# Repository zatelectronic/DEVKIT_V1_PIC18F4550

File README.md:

<div align="center">

# DEVKIT V1 PIC18F4550

**Kit de desenvolvimento profissional para o microcontrolador PIC18F4550 com USB nativo, programação via conector ICSP compatível com programador externo, reguladores 5V e 3,3V, oscilador SMD, botões RESET e BOOT, 2 LEDs de status e exposição completa de todos os ports GPIO**

</div>

---

## 📋 Índice

- [DEVKIT V1 PIC18F4550](#devkit-v1-pic18f4550)
  - [📋 Índice](#-índice)
  - [Visão Geral](#visão-geral)
  - [Renders 3D](#renders-3d)
  - [Arquitetura do Projeto](#arquitetura-do-projeto)
  - [Funcionalidades](#funcionalidades)
  - [Especificações Técnicas](#especificações-técnicas)
  - [Arquitetura de Alimentação](#arquitetura-de-alimentação)
  - [Interface USB Nativa](#interface-usb-nativa)
  - [Conector ICSP — Programação](#conector-icsp--programação)
    - [J5 — ICSP Principal (6 pinos angulado)](#j5--icsp-principal-6-pinos-angulado)
    - [J6 — Conector Auxiliar (3 pinos)](#j6--conector-auxiliar-3-pinos)
  - [Mapa Completo de Conectores e GPIO](#mapa-completo-de-conectores-e-gpio)
    - [J1 — Alimentação Externa (2 pinos)](#j1--alimentação-externa-2-pinos)
    - [J2 — Port RA (5 pinos)](#j2--port-ra-5-pinos)
    - [J3 — Port RC Superior (3 pinos)](#j3--port-rc-superior-3-pinos)
    - [J4 — Port RC Inferior (6 pinos)](#j4--port-rc-inferior-6-pinos)
    - [J7 — Port RE (4 pinos)](#j7--port-re-4-pinos)
    - [J8 — Port RB (4 pinos)](#j8--port-rb-4-pinos)
    - [J9 — Port RD (8 pinos)](#j9--port-rd-8-pinos)
    - [J10 — Alimentações (3 pinos)](#j10--alimentações-3-pinos)
  - [Lista de Materiais](#lista-de-materiais)
    - [Microcontrolador](#microcontrolador)
    - [USB Type-C e Alimentação](#usb-type-c-e-alimentação)
    - [Programador ICSP](#programador-icsp)
    - [Conectores GPIO](#conectores-gpio)
  - [Estrutura do Repositório](#estrutura-do-repositório)
  - [Como Usar](#como-usar)
    - [1. Gravando firmware via ICSP](#1-gravando-firmware-via-icsp)
    - [2. Alimentação](#2-alimentação)
    - [3. Modo Bootloader USB (BOOT)](#3-modo-bootloader-usb-boot)
    - [Exemplo de código — MPLAB XC8](#exemplo-de-código--mplab-xc8)
    - [Ferramentas recomendadas](#ferramentas-recomendadas)
  - [Sobre](#sobre)

---

## Visão Geral

**DEVKIT V1 PIC18F4550** é um kit de desenvolvimento completo para o microcontrolador **PIC18F4550-IPT** (TQFP-44 SMD), projetado pela **ZAT ELECTRONIC** utilizando **KiCad 10** com esquemático hierárquico dividido em quatro sub-folhas: **Microcontrolador**, **USB Type-C**, **Programador ICSP** e **Conexões GPIO**.

O PIC18F4550 é um microcontrolador de 8 bits da família PIC18 com **USB 2.0 Full Speed nativo** (RC4/D− e RC5/D+), memória Flash de 32KB, SRAM de 2KB e EEPROM de 256 bytes. O DEVKIT expõe todos os ports GPIO (RA, RB, RC, RD, RE) em conectores fêmea de 2,54mm, inclui reguladores de tensão **5V** e **3,3V** on-board, oscilador a cristal SMD de **8MHz**, botões **RESET** e **BOOT** tácteis SMD, **2 LEDs SMD** de status e conector **ICSP de 6 pinos** angulado compatível com programador externo.

> 💡 O modelo 3D do programador externo (`Microchip - PICkit3.stp`) está incluído no projeto — as imagens 3D mostram o DEVKIT conectado a um programador externo, evidenciando a integração direta pelo conector ICSP lateral.

---

## Renders 3D

<div align="center">

*Vista superior — PIC18F4550 TQFP-44, USB-C, cristal SMD, botões RESET/BOOT e conectores GPIO*

<br/>

*Vista isométrica — DEVKIT conectado ao programador externo pelo conector ICSP de 6 pinos*

<br/>

*Vista inferior isométrica — exposição completa dos ports RD (8 pinos) e RB (4 pinos) na borda inferior*

<br/>

*Visão completa do ecossistema — DEVKIT + programador externo para gravação de firmware*

</div>

---

## Arquitetura do Projeto

O projeto é organizado em **esquemático hierárquico** com 4 sub-folhas independentes:

```
DEVKIT_V1_PIC18F4550.kicad_sch  (folha raiz)
│
├── MICROCONTROLADOR.kicad_sch
│   ├── PIC18F4550-IPT (TQFP-44)
│   ├── Cristal 8MHz HC-49/SD SMD (KR1)
│   ├── Capacitores de cristal 22pF (C3, C4)
│   ├── Capacitor de desacoplamento USB 470nF (C5)
│   ├── Botão RESET táctil SMD (TACTIL_SWITCH1)
│   ├── Botão BOOT táctil SMD (TACTIL_SWITCH2)
│   ├── LEDs SMD 0805 — L1, L2
│   └── Resistores pull-up/proteção — R5, R6, R7
│
├── TYPE-C_USB.kicad_sch
│   ├── Conector USB-C (USB4105GFA SMD)
│   ├── Regulador 3,3V AMS1117-3.3 (U2 — SOT-223)
│   ├── Diodo Schottky SS1P3L (D1 — DO-220AA)
│   ├── Capacitores eletrolíticos 10µF/16V (C2, C8)
│   ├── Capacitores de desacoplamento 100nF (C1, C6)
│   ├── Resistores CC 5,1KΩ (R3, R4 — para USB-C)
│   ├── Resistores 1KΩ e 0Ω (R1, R2)
│   └── LED SMD (L1 — status alimentação)
│
├── PROGRAMADOR.kicad_sch
│   ├── Conector ICSP 6 pinos angulado (J5)
│   ├── Conector auxiliar de programação (J6)
│   └── Resistores pull-up 10KΩ (R8, R9)
│
└── CONEXÕES.kicad_sch
    ├── J1  — Conector alimentação +5V/GND (2 pinos)
    ├── J2  — Port RA (5 pinos: RA0–RA5)
    ├── J3  — Port RC superior (3 pinos: RC0–RC2)
    ├── J4  — Port RC inferior (6 pinos: RC6, RC7)
    ├── J7  — Port RE (4 pinos: RE0–RE2)
    ├── J8  — Port RB (4 pinos: RB0–RB3)
    ├── J9  — Port RD (8 pinos: RD0–RD7)
    └── J10 — Alimentações (3 pinos: +5V / +3,3V / GND)
```

---

## Funcionalidades

- ✅ **PIC18F4550-IPT** (TQFP-44 SMD) — MCU 8 bits, 32KB Flash, 2KB SRAM, 256B EEPROM
- ✅ **USB 2.0 Full Speed nativo** — RC4/D− e RC5/D+ conectados ao conector USB-C
- ✅ **Conector USB-C** (USB4105GFA SMD) — entrada moderna com resistores CC 5,1KΩ
- ✅ **Regulador 3,3V** (AMS1117-3.3 SOT-223) — saída 3,3V para periféricos de baixa tensão
- ✅ **Alimentação 5V** via USB-C ou conector externo J1
- ✅ **Cristal 8MHz SMD** (HC-49/SD) — oscilador externo de alta estabilidade
- ✅ **Botão RESET** (TACTIL_SWITCH1 — SMD 6×6×6mm) — reset do microcontrolador
- ✅ **Botão BOOT** (TACTIL_SWITCH2 — SMD 6×6×6mm) — entrada em modo bootloader USB
- ✅ **2 LEDs SMD 0805** (L1, L2) — indicadores de status programáveis
- ✅ **Conector ICSP J5** — 6 pinos angulado para programador externo (PGC, PGD, MCLR, VDD, VSS, VPP)
- ✅ **Conector auxiliar J6** — 3 pinos (+5V / PGM / GND) para programação low-voltage
- ✅ **Diodo Schottky SS1P3L** (DO-220AA) — proteção na linha VBUS
- ✅ **Todos os ports GPIO expostos** — RA, RB, RC, RD, RE em conectores fêmea 2,54mm
- ✅ **Capacitores de desacoplamento** distribuídos — C3, C4, C5, C6 (0805 SMD)
- ✅ **Capacitores eletrolíticos** C2, C7, C8 (EIA-3216 SMD) — filtragem de alimentação
- ✅ **4 furos de fixação** — montagem em painéis e caixas
- ✅ **Esquemático hierárquico** em 4 sub-folhas — organização profissional do projeto

---

## Especificações Técnicas

| Parâmetro | Valor |
|-----------|-------|
| **Microcontrolador** | PIC18F4550-IPT |
| **Encapsulamento MCU** | TQFP-44 (10×10mm, passo 0,8mm) |
| **Arquitetura** | 8 bits — PIC18 |
| **Memória Flash** | 32 KB |
| **SRAM** | 2 KB |
| **EEPROM** | 256 bytes |
| **USB** | Full Speed 2.0 nativo (12 Mbps) |
| **Clock** | 8 MHz (cristal externo HC-49/SD SMD) |
| **Tensão de operação** | 2,0V – 5,5V |
| **Tensão da placa** | 5V (USB-C ou J1) |
| **Regulador 3,3V** | AMS1117-3.3 (SOT-223) |
| **Conector USB** | USB-C — USB4105GFA SMD |
| **Conector ICSP** | 6 pinos angulado (PGC/PGD/MCLR/VDD/VSS/VPP) |
| **GPIO exposto** | RA (5), RB (4), RC (7), RD (8), RE (3) = 27 pinos |
| **Botões** | RESET + BOOT (SMD táctil 6×6×6mm) |
| **LEDs** | 2x SMD 0805 |
| **Resistores** | SMD 1206 |
| **Capacitores** | SMD 0805 + EIA-3216 |
| **Ferramenta de Projeto** | KiCad 10 — esquemático hierárquico |
| **Tipo de montagem** | SMD |

---

## Arquitetura de Alimentação

```
USB-C (VBUS 5V)
      │
  [SS1P3L D1]  ← Proteção Schottky
      │
     5V ──────────────────────────────────► J1 (+5V)
      │                                     J10 (+5V)
      │                                     VDD do PIC18F4550
      │
  [AMS1117-3.3 U2]
      │
    3,3V ────────────────────────────────► J10 (+3,3V)
                                           Periféricos 3,3V

Alimentação alternativa:
J1 (+5V / GND) ──► entrada direta de fonte externa 5V
```

---

## Interface USB Nativa

O PIC18F4550 possui **USB 2.0 Full Speed integrado** no próprio chip, sem necessidade de conversor externo:

```
USB-C (USB4105GFA)
    │
    ├── D− (CC1/CC2 com 5,1KΩ) ──► RC4/D− do PIC18F4550
    └── D+ (CC1/CC2 com 5,1KΩ) ──► RC5/D+ do PIC18F4550

R3, R4 (5,1KΩ) — resistores CC para identificação USB-C
C5 (470nF)     — capacitor de desacoplamento USB do PIC
```

> 💡 Para utilizar o USB, o firmware deve implementar a pilha USB do PIC18F4550 via bibliotecas como **Microchip USB Framework** ou **USB CDC** para comunicação serial virtual.

---

## Conector ICSP — Programação

O DEVKIT possui conector **ICSP de 6 pinos angulado (J5)** compatível com programador externo e conectores adicionais:

### J5 — ICSP Principal (6 pinos angulado)

| Pino | Sinal | Descrição |
|------|-------|-----------|
| 1 | PGC | Clock de programação (ICSP Clock) |
| 2 | PGD | Dado de programação (ICSP Data) |
| 3 | VSS | GND |
| 4 | VDD | +5V |
| 5 | VPP | Tensão de programação / MCLR |
| 6 | — | (não conectado) |

### J6 — Conector Auxiliar (3 pinos)

| Pino | Sinal | Descrição |
|------|-------|-----------|
| 1 | +5V | Alimentação |
| 2 | PGM | Low-Voltage Programming |
| 3 | GND | Terra |

> 🔴 Para programar com **programador externo** (ex: PICkit 3/4, ICD): conecte o cabo ICSP no conector J5. O modelo 3D do programador está incluído no projeto para visualização do encaixe.

---

## Mapa Completo de Conectores e GPIO

### J1 — Alimentação Externa (2 pinos)

| Pino | Sinal |
|------|-------|
| 1 | +5V |
| 2 | GND |

### J2 — Port RA (5 pinos)

| Pino | GPIO | Função alternativa |
|------|------|--------------------|
| 1 | RA0 | AN0 / ADC |
| 2 | RA1 | AN1 / ADC |
| 3 | RA2 | AN2 / VREF− |
| 4 | RA3 | AN3 / VREF+ |
| 5 | RA4 | T0CKI / C1OUT |
| 6 | RA5 | AN4 / SS / HLVDIN |

### J3 — Port RC Superior (3 pinos)

| Pino | GPIO | Função alternativa |
|------|------|--------------------|
| 1 | RC0 | T1OSO / T1CKI |
| 2 | RC1 | T1OSI / CCP2 |
| 3 | RC2 | CCP1 |

### J4 — Port RC Inferior (6 pinos)

| Pino | GPIO | Função alternativa |
|------|------|--------------------|
| 1 | RC6 | TX / CK (USART) |
| 2 | RC7 | RX / DT (USART) |

### J7 — Port RE (4 pinos)

| Pino | GPIO | Função alternativa |
|------|------|--------------------|
| 1 | RE0 | AN5 / RD |
| 2 | RE1 | AN6 / WR |
| 3 | RE2 | AN7 / CS |

### J8 — Port RB (4 pinos)

| Pino | GPIO | Função alternativa |
|------|------|--------------------|
| 1 | RB0 | INT0 / FLT0 / AN12 |
| 2 | RB1 | INT1 / AN10 |
| 3 | RB2 | INT2 / AN8 |
| 4 | RB3 | AN9 / CCP2 |

### J9 — Port RD (8 pinos)

| Pino | GPIO | Função alternativa |
|------|------|--------------------|
| 1 | RD0 | PSP0 |
| 2 | RD1 | PSP1 |
| 3 | RD2 | PSP2 |
| 4 | RD3 | PSP3 |
| 5 | RD4 | PSP4 |
| 6 | RD5 | PSP5 |
| 7 | RD6 | PSP6 |
| 8 | RD7 | PSP7 |

### J10 — Alimentações (3 pinos)

| Pino | Sinal |
|------|-------|
| 1 | +5V |
| 2 | +3,3V |
| 3 | GND |

---

## Lista de Materiais

### Microcontrolador

| Ref | Componente | Valor | Encapsulamento |
|-----|-----------|-------|----------------|
| U1 | Microcontrolador | PIC18F4550-IPT | TQFP-44 SMD |
| KR1 | Cristal | 8MHz | HC-49/SD SMD |
| C3, C4 | Capacitor cristal | 22pF | 0805 SMD |
| C5 | Capacitor USB | 470nF / 50V | 0805 SMD |
| TACTIL_SWITCH1 | Botão RESET | 6×6×6mm | SMD táctil |
| TACTIL_SWITCH2 | Botão BOOT | 6×6×6mm | SMD táctil |
| L1, L2 | LED status | SMD 0805 | 0805 SMD |
| R5 | Resistor LED | 1KΩ | 1206 SMD |
| R6 | Resistor pull-up MCLR | 10KΩ | 1206 SMD |
| R7 | Resistor pull-up BOOT | 10KΩ | 1206 SMD |

### USB Type-C e Alimentação

| Ref | Componente | Valor | Encapsulamento |
|-----|-----------|-------|----------------|
| USBC1 | Conector USB-C | USB4105GFA | SMD |
| U2 | Regulador 3,3V | AMS1117-3.3 | SOT-223 SMD |
| D1 | Diodo Schottky | SS1P3L | DO-220AA SMD |
| C1, C6 | Capacitor desacoplamento | 100nF / 50V | 0805 SMD |
| C2, C8 | Capacitor eletrolítico | 10µF / 16V | EIA-3216 SMD |
| C7 | Capacitor eletrolítico | 10µF / 16V | EIA-3216 SMD |
| R1 | Resistor | 0Ω (jumper) | 1206 SMD |
| R2 | Resistor | 1KΩ | 1206 SMD |
| R3, R4 | Resistores CC USB-C | 5,1KΩ | 1206 SMD |

### Programador ICSP

| Ref | Componente | Valor | Encapsulamento |
|-----|-----------|-------|----------------|
| J5 | Conector ICSP | 6 pinos angulado | Header 2,54mm |
| J6 | Conector auxiliar | 3 pinos | Header 2,54mm |
| R8 | Resistor pull-up PGC | 10KΩ | 1206 SMD |
| R9 | Resistor pull-up PGD | 10KΩ | 1206 SMD |

### Conectores GPIO

| Ref | Descrição | Pinos |
|-----|-----------|-------|
| J1 | Alimentação externa | 2 pinos (2,54mm angulado) |
| J2 | Port RA | 5 pinos fêmea 2,54mm |
| J3 | Port RC superior | 3 pinos fêmea 2,54mm |
| J4 | Port RC inferior | 6 pinos fêmea 2,54mm |
| J7 | Port RE | 4 pinos fêmea 2,54mm |
| J8 | Port RB | 4 pinos fêmea 2,54mm |
| J9 | Port RD | 8 pinos fêmea 2,54mm |
| J10 | Alimentações | 3 pinos fêmea 2,54mm |

---

## Estrutura do Repositório

```
DEVKIT_V1_PIC18F4550/
├── DEVKIT_V1_PIC18F4550.kicad_pro    # Arquivo de projeto KiCad
├── DEVKIT_V1_PIC18F4550.kicad_sch    # Esquemático raiz (hierárquico)
├── DEVKIT_V1_PIC18F4550.kicad_pcb    # Layout da PCB (KiCad 10)
├── DEVKIT_V1_PIC18F4550.kicad_prl    # Configurações locais
├── MICROCONTROLADOR.kicad_sch        # Sub-folha: MCU + cristal + botões + LEDs
├── TYPE-C_USB.kicad_sch              # Sub-folha: USB-C + reguladores + proteção
├── PROGRAMADOR.kicad_sch             # Sub-folha: ICSP + conector programador
├── CONEXÕES.kicad_sch                # Sub-folha: todos os conectores GPIO
├── PIC18F4550_DATASHEET.pdf          # Datasheet oficial do PIC18F4550
├── packages3D/                       # Modelos 3D arquivados (STEP / WRL)
│   ├── TQFP-44_10x10mm_P0.8mm.wrl
│   ├── USB4105GFA.STEP
│   ├── SOT-223.wrl
│   ├── Crystal_SMD_HC49-SD.wrl
│   ├── Tactal Switch - SMD 6x6x6.stp
│   ├── LED_0805_2012Metric.wrl
│   ├── D_SMP_DO-220AA.wrl
│   ├── Microchip - PICkit3.stp
│   ├── PinHeader_6X1_right.stp
│   ├── PinHeader_2X1_right.stp
│   └── *-Pin Header - Female - 2.54mm.step
├── fp-info-cache                     # Cache de footprints
├── imagem_1.png                      # Render 3D superior
├── imagem_2.png                      # Render 3D isométrico com programador
├── imagem_3.png                      # Render 3D traseiro
├── imagem_4.png                      # Render 3D completo com programador
└── README.md
```

---

## Como Usar

### 1. Gravando firmware via ICSP

1. Conecte o programador externo ao conector **J5** (6 pinos angulado)
2. Abra o **MPLAB X IDE** e configure o projeto para **PIC18F4550**
3. Selecione o programador (ex: PICkit 3/4) e clique em **Make and Program Device**
4. O LED de status confirmará o sucesso da gravação

### 2. Alimentação

```
Opção A — Via USB-C:
  Conecte cabo USB-C → alimentação automática 5V via VBUS

Opção B — Via conector externo J1:
  Aplique +5V no pino 1 e GND no pino 2 do conector J1
```

### 3. Modo Bootloader USB (BOOT)

```
1. Mantenha o botão BOOT pressionado
2. Pressione e solte o botão RESET
3. Solte o botão BOOT
4. O PIC18F4550 entrará em modo bootloader USB
5. Grave o firmware via software de bootloader (ex: HIDBootloader)
```

### Exemplo de código — MPLAB XC8

```c
#include <xc.h>

// Configurações básicas do PIC18F4550
#pragma config FOSC = HS        // Oscilador externo HS
#pragma config WDT = OFF        // Watchdog desabilitado
#pragma config MCLRE = ON       // MCLR ativo
#pragma config LVP = OFF        // Low-voltage programming off
#pragma config PBADEN = OFF     // PORTB digital

#define _XTAL_FREQ 8000000

void main(void) {
    TRISDbits.TRISD0 = 0;   // RD0 como saída (J9 pino 1)
    TRISDbits.TRISD1 = 0;   // RD1 como saída (J9 pino 2)

    while(1) {
        LATDbits.LATD0 = 1;  // RD0 HIGH
        __delay_ms(500);
        LATDbits.LATD0 = 0;  // RD0 LOW
        __delay_ms(500);
    }
}
```

### Ferramentas recomendadas

| Ferramenta | Finalidade |
|------------|-----------|
| MPLAB X IDE | IDE oficial para desenvolvimento PIC |
| XC8 Compiler | Compilador C para PIC de 8 bits |
| Programador externo | Gravação via ICSP (J5) |
| MPLAB Code Configurator | Geração automática de configuração de periféricos |
| Microchip USB Framework | Implementação da pilha USB do PIC18F4550 |

---

## Sobre

<div align="center">

Projetado por **ZAT ELECTRONIC**

*DEVKIT V1 PIC18F4550 — Made in Brazil 🇧🇷*

</div>

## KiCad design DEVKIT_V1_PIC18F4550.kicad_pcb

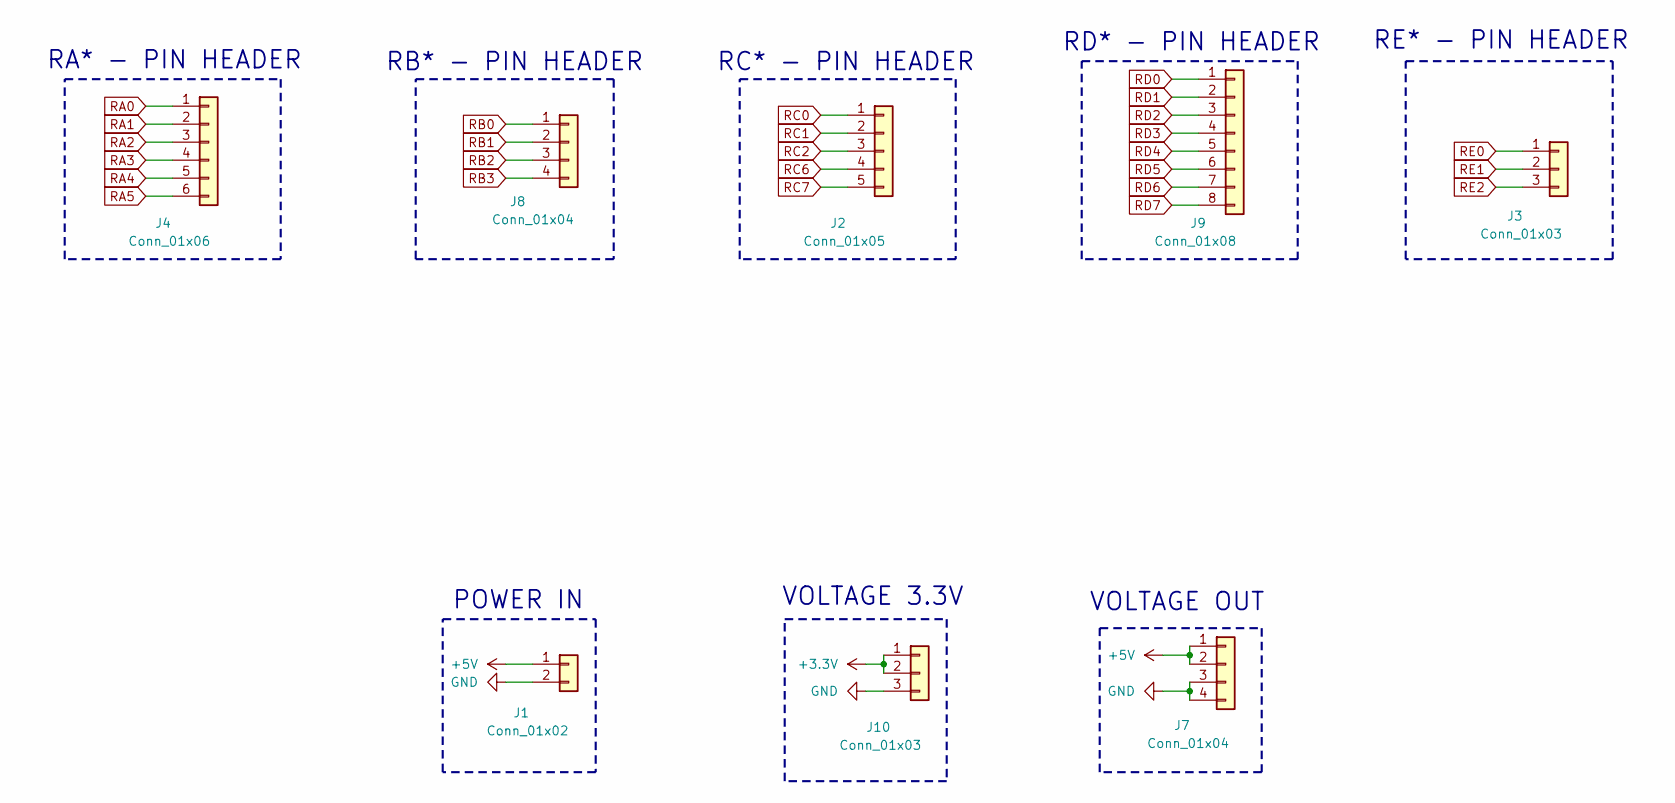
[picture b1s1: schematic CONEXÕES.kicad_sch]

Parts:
J1: Conn_01x02; PinHeader_1x02_P2.54mm_Vertical
J2: Conn_01x05; PinHeader_1x05_P2.54mm_Vertical
J3, J10: Conn_01x03; PinHeader_1x03_P2.54mm_Vertical
J4: Conn_01x06; PinHeader_1x06_P2.54mm_Vertical
J7, J8: Conn_01x04; PinHeader_1x04_P2.54mm_Vertical
J9: Conn_01x08; PinHeader_1x08_P2.54mm_Vertical

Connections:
+3.3V: J10.1, J10.2; also elsewhere on the board
+5V: J1.1, J7.1, J7.2; also elsewhere on the board
GND: J1.2, J7.3, J7.4, J10.3; also elsewhere on the board
RA0: J4.1; also elsewhere on the board
RA1: J4.2; also elsewhere on the board
RA2: J4.3; also elsewhere on the board
RA3: J4.4; also elsewhere on the board
RA4: J4.5; also elsewhere on the board
RA5: J4.6; also elsewhere on the board
RB0: J8.1; also elsewhere on the board
RB1: J8.2; also elsewhere on the board
RB2: J8.3; also elsewhere on the board
RB3: J8.4; also elsewhere on the board
RC0: J2.1; also elsewhere on the board
RC1: J2.2; also elsewhere on the board
RC2: J2.3; also elsewhere on the board
RC6: J2.4; also elsewhere on the board
RC7: J2.5; also elsewhere on the board
RD0: J9.1; also elsewhere on the board
RD1: J9.2; also elsewhere on the board
RD2: J9.3; also elsewhere on the board
RD3: J9.4; also elsewhere on the board
RD4: J9.5; also elsewhere on the board
RD5: J9.6; also elsewhere on the board
RD6: J9.7; also elsewhere on the board
RD7: J9.8; also elsewhere on the board
RE0: J3.1; also elsewhere on the board
RE1: J3.2; also elsewhere on the board
RE2: J3.3; also elsewhere on the board

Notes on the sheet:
VOLTAGE 3.3V
POWER IN
RC* - PIN HEADER
RB* - PIN HEADER
VOLTAGE OUT
RD* - PIN HEADER
RE* - PIN HEADER
RA* - PIN HEADER

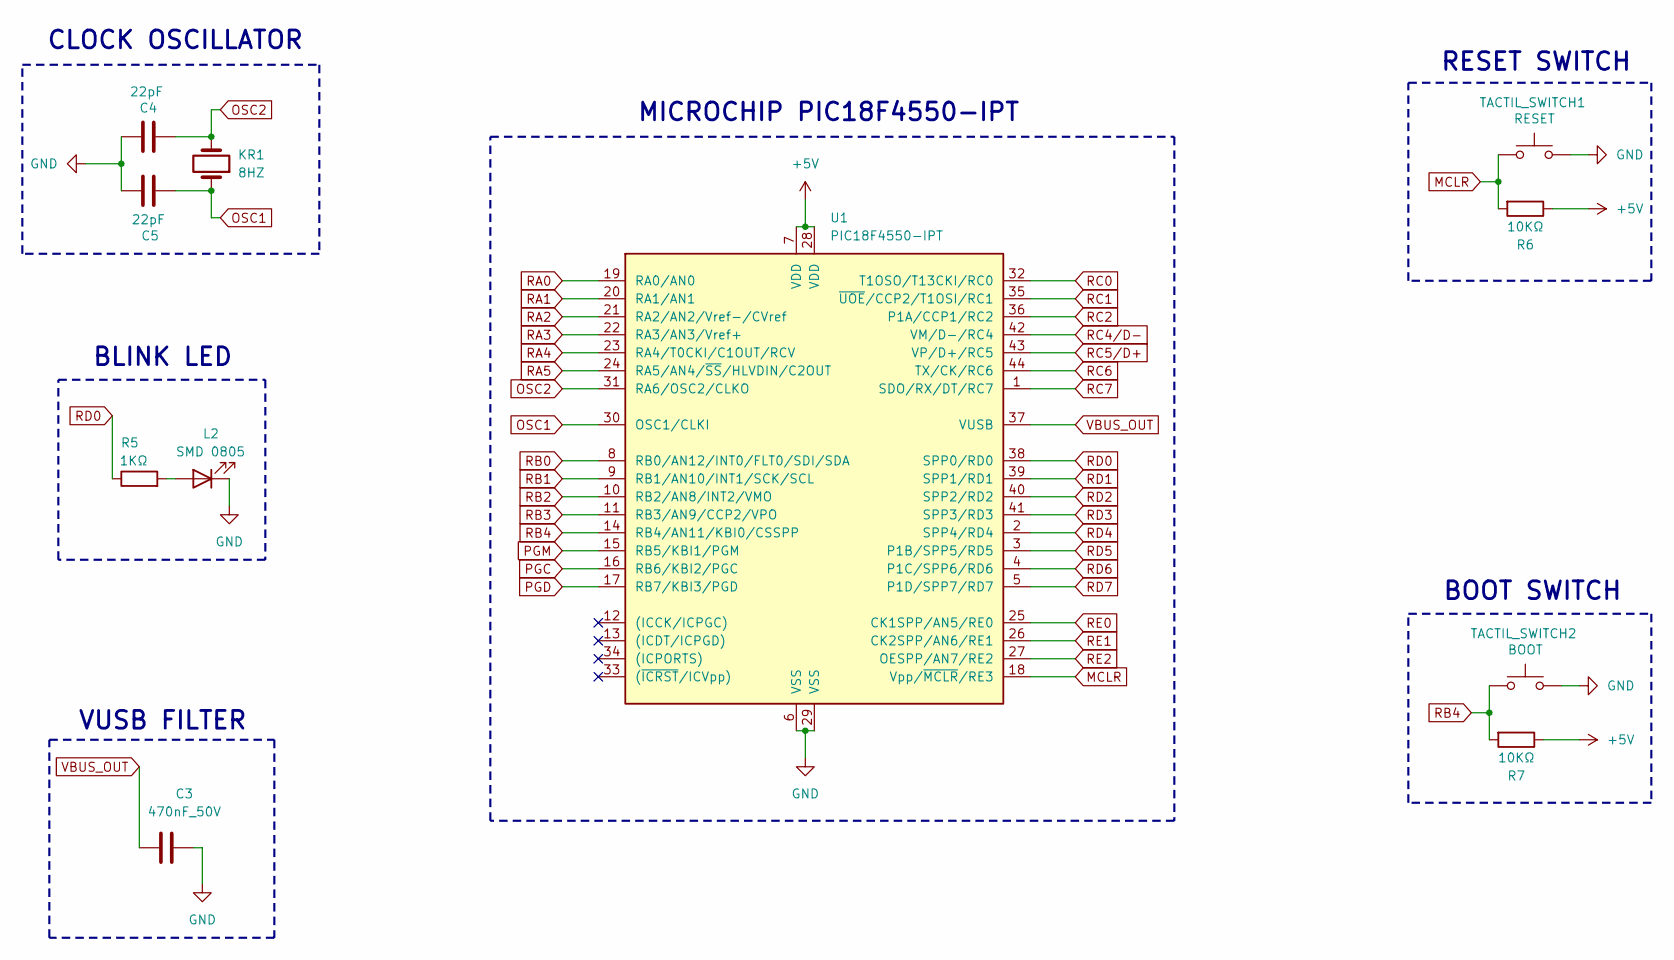
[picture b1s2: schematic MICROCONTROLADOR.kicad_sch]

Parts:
C3: 470nF_50V; C_0805_2012Metric
C4, C5: 22pF; C_0805_2012Metric
KR1: 8HZ; Crystal_SMD_HC49-SD
L2: SMD 0805; LED_0805_2012Metric
R5: 1KΩ; R_1206_3216Metric
R6, R7: 10KΩ; R_1206_3216Metric
TACTIL_SWITCH1: RESET; SW_Push_1P1T_NO_6x6mm_H9.5mm
TACTIL_SWITCH2: BOOT; SW_Push_1P1T_NO_6x6mm_H9.5mm
U1: PIC18F4550-IPT; TQFP-44_10x10mm_P0.8mm

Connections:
+5V: R6.1, R7.1, U1.7 (VDD), U1.28 (VDD); also elsewhere on the board
GND: C3.1, C4.2, C5.2, L2.1 (K), TACTIL_SWITCH1.2, TACTIL_SWITCH2.2, U1.6 (VSS), U1.29 (VSS); also elsewhere on the board
MCLR: R6.2, TACTIL_SWITCH1.1, U1.18 (Vpp/~MCLR/RE3); also elsewhere on the board
unnamed: L2.2 (A), R5.2
OSC1: C5.1, KR1.1, U1.30 (OSC1/CLKI)
OSC2: C4.1, KR1.2, U1.31 (RA6/OSC2/CLKO)
PGC: U1.16 (RB6/KBI2/PGC); also elsewhere on the board
PGD: U1.17 (RB7/KBI3/PGD); also elsewhere on the board
PGM: U1.15 (RB5/KBI1/PGM); also elsewhere on the board
RA0: U1.19 (RA0/AN0); also elsewhere on the board
RA1: U1.20 (RA1/AN1); also elsewhere on the board
RA2: U1.21 (RA2/AN2/Vref-/CVref); also elsewhere on the board
RA3: U1.22 (RA3/AN3/Vref+); also elsewhere on the board
RA4: U1.23 (RA4/T0CKI/C1OUT/RCV); also elsewhere on the board
RA5: U1.24 (RA5/AN4/~SS/HLVDIN/C2OUT); also elsewhere on the board
RB0: U1.8 (RB0/AN12/INT0/FLT0/SDI/SDA); also elsewhere on the board
RB1: U1.9 (RB1/AN10/INT1/SCK/SCL); also elsewhere on the board
RB2: U1.10 (RB2/AN8/INT2/VMO); also elsewhere on the board
RB3: U1.11 (RB3/AN9/CCP2/VPO); also elsewhere on the board
RB4: R7.2, TACTIL_SWITCH2.1, U1.14 (RB4/AN11/KBI0/CSSPP)
RC0: U1.32 (T1OSO/T13CKI/RC0); also elsewhere on the board
RC1: U1.35 (~UOE/CCP2/T1OSI/RC1); also elsewhere on the board
RC2: U1.36 (P1A/CCP1/RC2); also elsewhere on the board
RC4/D-: U1.42 (VM/D-/RC4); also elsewhere on the board
RC5/D+: U1.43 (VP/D+/RC5); also elsewhere on the board
RC6: U1.44 (TX/CK/RC6); also elsewhere on the board
RC7: U1.1 (SDO/RX/DT/RC7); also elsewhere on the board
RD0: R5.1, U1.38 (SPP0/RD0); also elsewhere on the board
RD1: U1.39 (SPP1/RD1); also elsewhere on the board
RD2: U1.40 (SPP2/RD2); also elsewhere on the board
RD3: U1.41 (SPP3/RD3); also elsewhere on the board
RD4: U1.2 (SPP4/RD4); also elsewhere on the board
RD5: U1.3 (P1B/SPP5/RD5); also elsewhere on the board
RD6: U1.4 (P1C/SPP6/RD6); also elsewhere on the board
RD7: U1.5 (P1D/SPP7/RD7); also elsewhere on the board
RE0: U1.25 (CK1SPP/AN5/RE0); also elsewhere on the board
RE1: U1.26 (CK2SPP/AN6/RE1); also elsewhere on the board
RE2: U1.27 (OESPP/AN7/RE2); also elsewhere on the board
VBUS_OUT: C3.2, U1.37 (VUSB); also elsewhere on the board

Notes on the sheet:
CLOCK OSCILLATOR
BLINK LED
VUSB FILTER
BOOT SWITCH
MICROCHIP PIC18F4550-IPT
RESET SWITCH

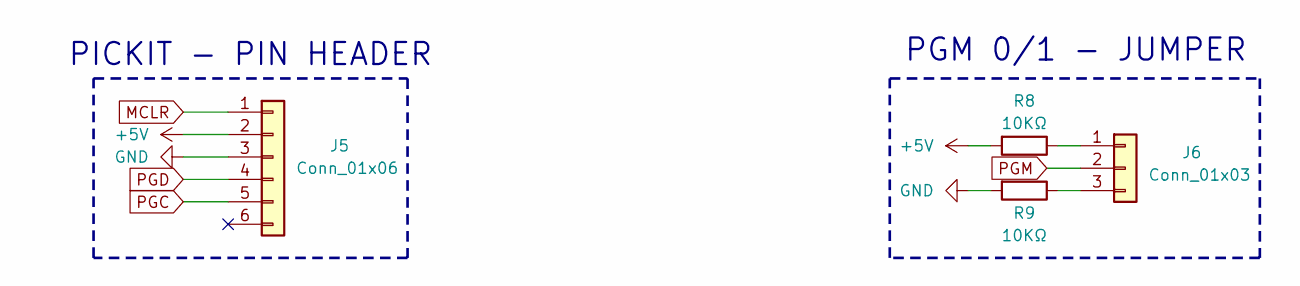
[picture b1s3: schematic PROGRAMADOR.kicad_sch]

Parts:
J5: Conn_01x06; PinHeader_1x06_P2.54mm_Vertical
J6: Conn_01x03; PinHeader_1x03_P2.54mm_Vertical
R8, R9: 10KΩ; R_1206_3216Metric

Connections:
+5V: J5.2, R8.2; also elsewhere on the board
GND: J5.3, R9.2; also elsewhere on the board
MCLR: J5.1; also elsewhere on the board
unnamed: J6.1, R8.1
unnamed: J6.3, R9.1
PGC: J5.5; also elsewhere on the board
PGD: J5.4; also elsewhere on the board
PGM: J6.2; also elsewhere on the board

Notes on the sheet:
PGM 0/1 - JUMPER
PICKIT - PIN HEADER

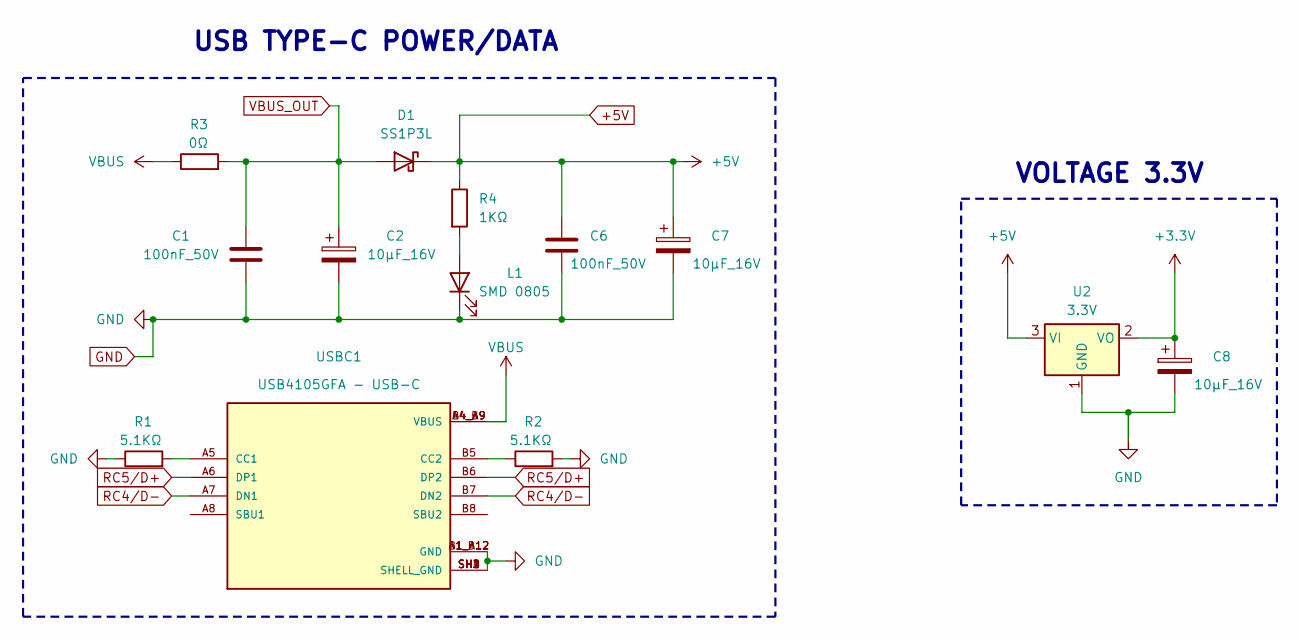
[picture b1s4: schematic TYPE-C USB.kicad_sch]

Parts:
C1, C6: 100nF_50V; C_0805_2012Metric
C2, C7, C8: 10μF_16V; CP_EIA-3216-18_Kemet-A
D1: SS1P3L; D_SMP_DO-220AA
L1: SMD 0805; LED_0805_2012Metric
R1, R2: 5.1KΩ; R_1206_3216Metric
R3: 0Ω; R_1206_3216Metric
R4: 1KΩ; R_1206_3216Metric
U2: 3.3V; SOT-223-3_TabPin2
USBC1: USB4105GFA - USB-C; USB4105GFA; PARTREV B3

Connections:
+3.3V: C8.1, U2.2 (VO); also elsewhere on the board
+5V: C6.1, C7.1, D1.1 (K), R4.1, U2.3 (VI); also elsewhere on the board
GND: C1.2, C2.2, C6.2, C7.2, C8.2, L1.1 (K), R1.1, R2.2, U2.1 (GND), USBC1.A1_B12 (GND), USBC1.B1_A12 (GND), USBC1.SH1 (SHELL_GND), USBC1.SH2 (SHELL_GND), USBC1.SH3 (SHELL_GND), USBC1.SH4 (SHELL_GND); also elsewhere on the board
unnamed: L1.2 (A), R4.2
unnamed: R1.2, USBC1.A5 (CC1)
unnamed: R2.1, USBC1.B5 (CC2)
RC4/D-: USBC1.A7 (DN1), USBC1.B7 (DN2); also elsewhere on the board
RC5/D+: USBC1.A6 (DP1), USBC1.B6 (DP2); also elsewhere on the board
VBUS: R3.1, USBC1.A4_B9 (VBUS), USBC1.B4_A9 (VBUS)
VBUS_OUT: C1.1, C2.1, D1.2 (A), R3.2; also elsewhere on the board

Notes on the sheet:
VOLTAGE 3.3V
USB TYPE-C POWER/DATA

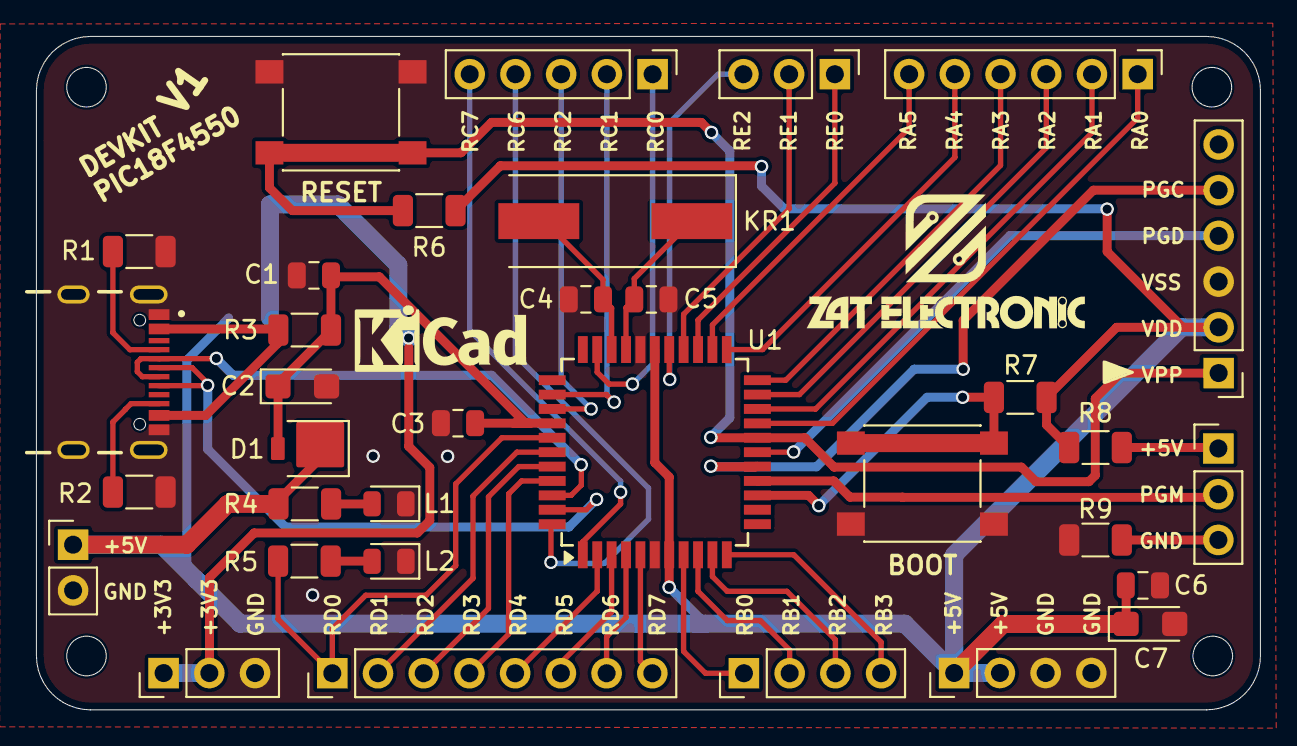
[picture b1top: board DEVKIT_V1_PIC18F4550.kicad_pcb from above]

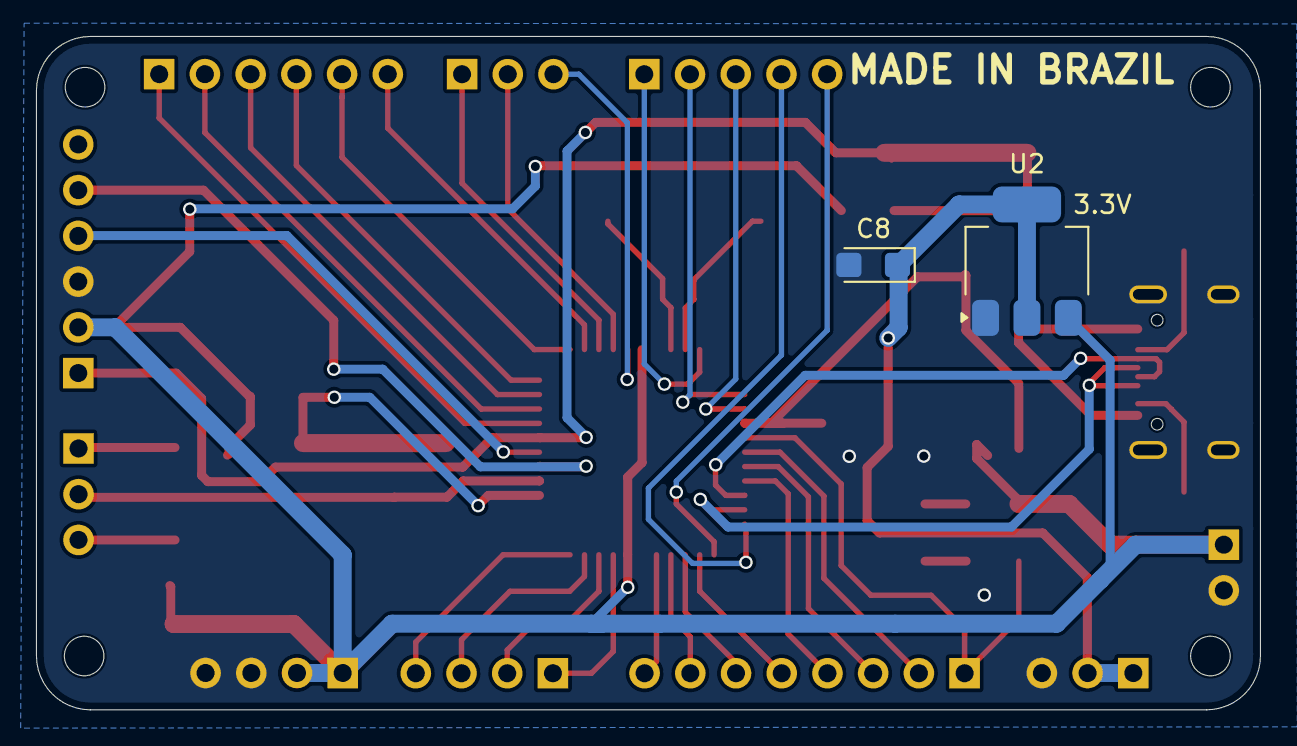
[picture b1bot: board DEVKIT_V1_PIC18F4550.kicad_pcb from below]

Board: 4 copper layers, 68.0 x 37.4 mm, 36 parts (2 on the bottom side), 46 nets.

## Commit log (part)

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2026-06-28 commit_3
2026-06-29 COMMIT-4
